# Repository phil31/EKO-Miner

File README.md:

# EKO-Miner

repository of EKO Miner designs

#### Inspired by the [Bitaxe](https://github.com/skot/bitaxe) and [OSMU fundation] (https://osmu.wiki/)

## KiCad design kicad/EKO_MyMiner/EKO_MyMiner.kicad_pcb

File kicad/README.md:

## BOX Miner

#### The EKO-Miner is a stackable and rackable ASIC Bitcoin miner that utilizes hashcards. The hashcards are capable of mining Bitcoin by themselves or multiple. The concept of hashcards is highly scalable and offers a clean and streamlined approach to Bitcoin mining.

Miner Box Supports up to 3 ASIC Hashcards. An ATX PSU is required.

- Rackable miner boards based on specifics ASIC Hashboards, generic power supply and driven by an ESP32
- WIFI and ETHERNET connectivity
- TFT RGB LCD 172x320 display
- External standard ATX power supply
- Watercooling for quiet operation

Power board : 
	- designed with TPS53667 / 5 Phases / 0.5 to 2.5V, up to 300Watts

AsicBoards : 
- 16 x BM1366 : 8 TH/s - Efficiency 25J/TH
- 16 x BM1368 : 9.5 TH/s - Efficiency 18J/TH
- 10 x BM1370 : 10 TH/s - Efficiency 15J/TH
	
enclosure box dimensions: 200 x 200 x 140 mm

## NerdEKO-GammaFork-NoATX Miner
fork of the NerdOCTAXE-Gamma design (https://github.com/Patsch91/NerdOCTAXE-Gamma), with 12 x BM1370 (12TH/s SHA256)

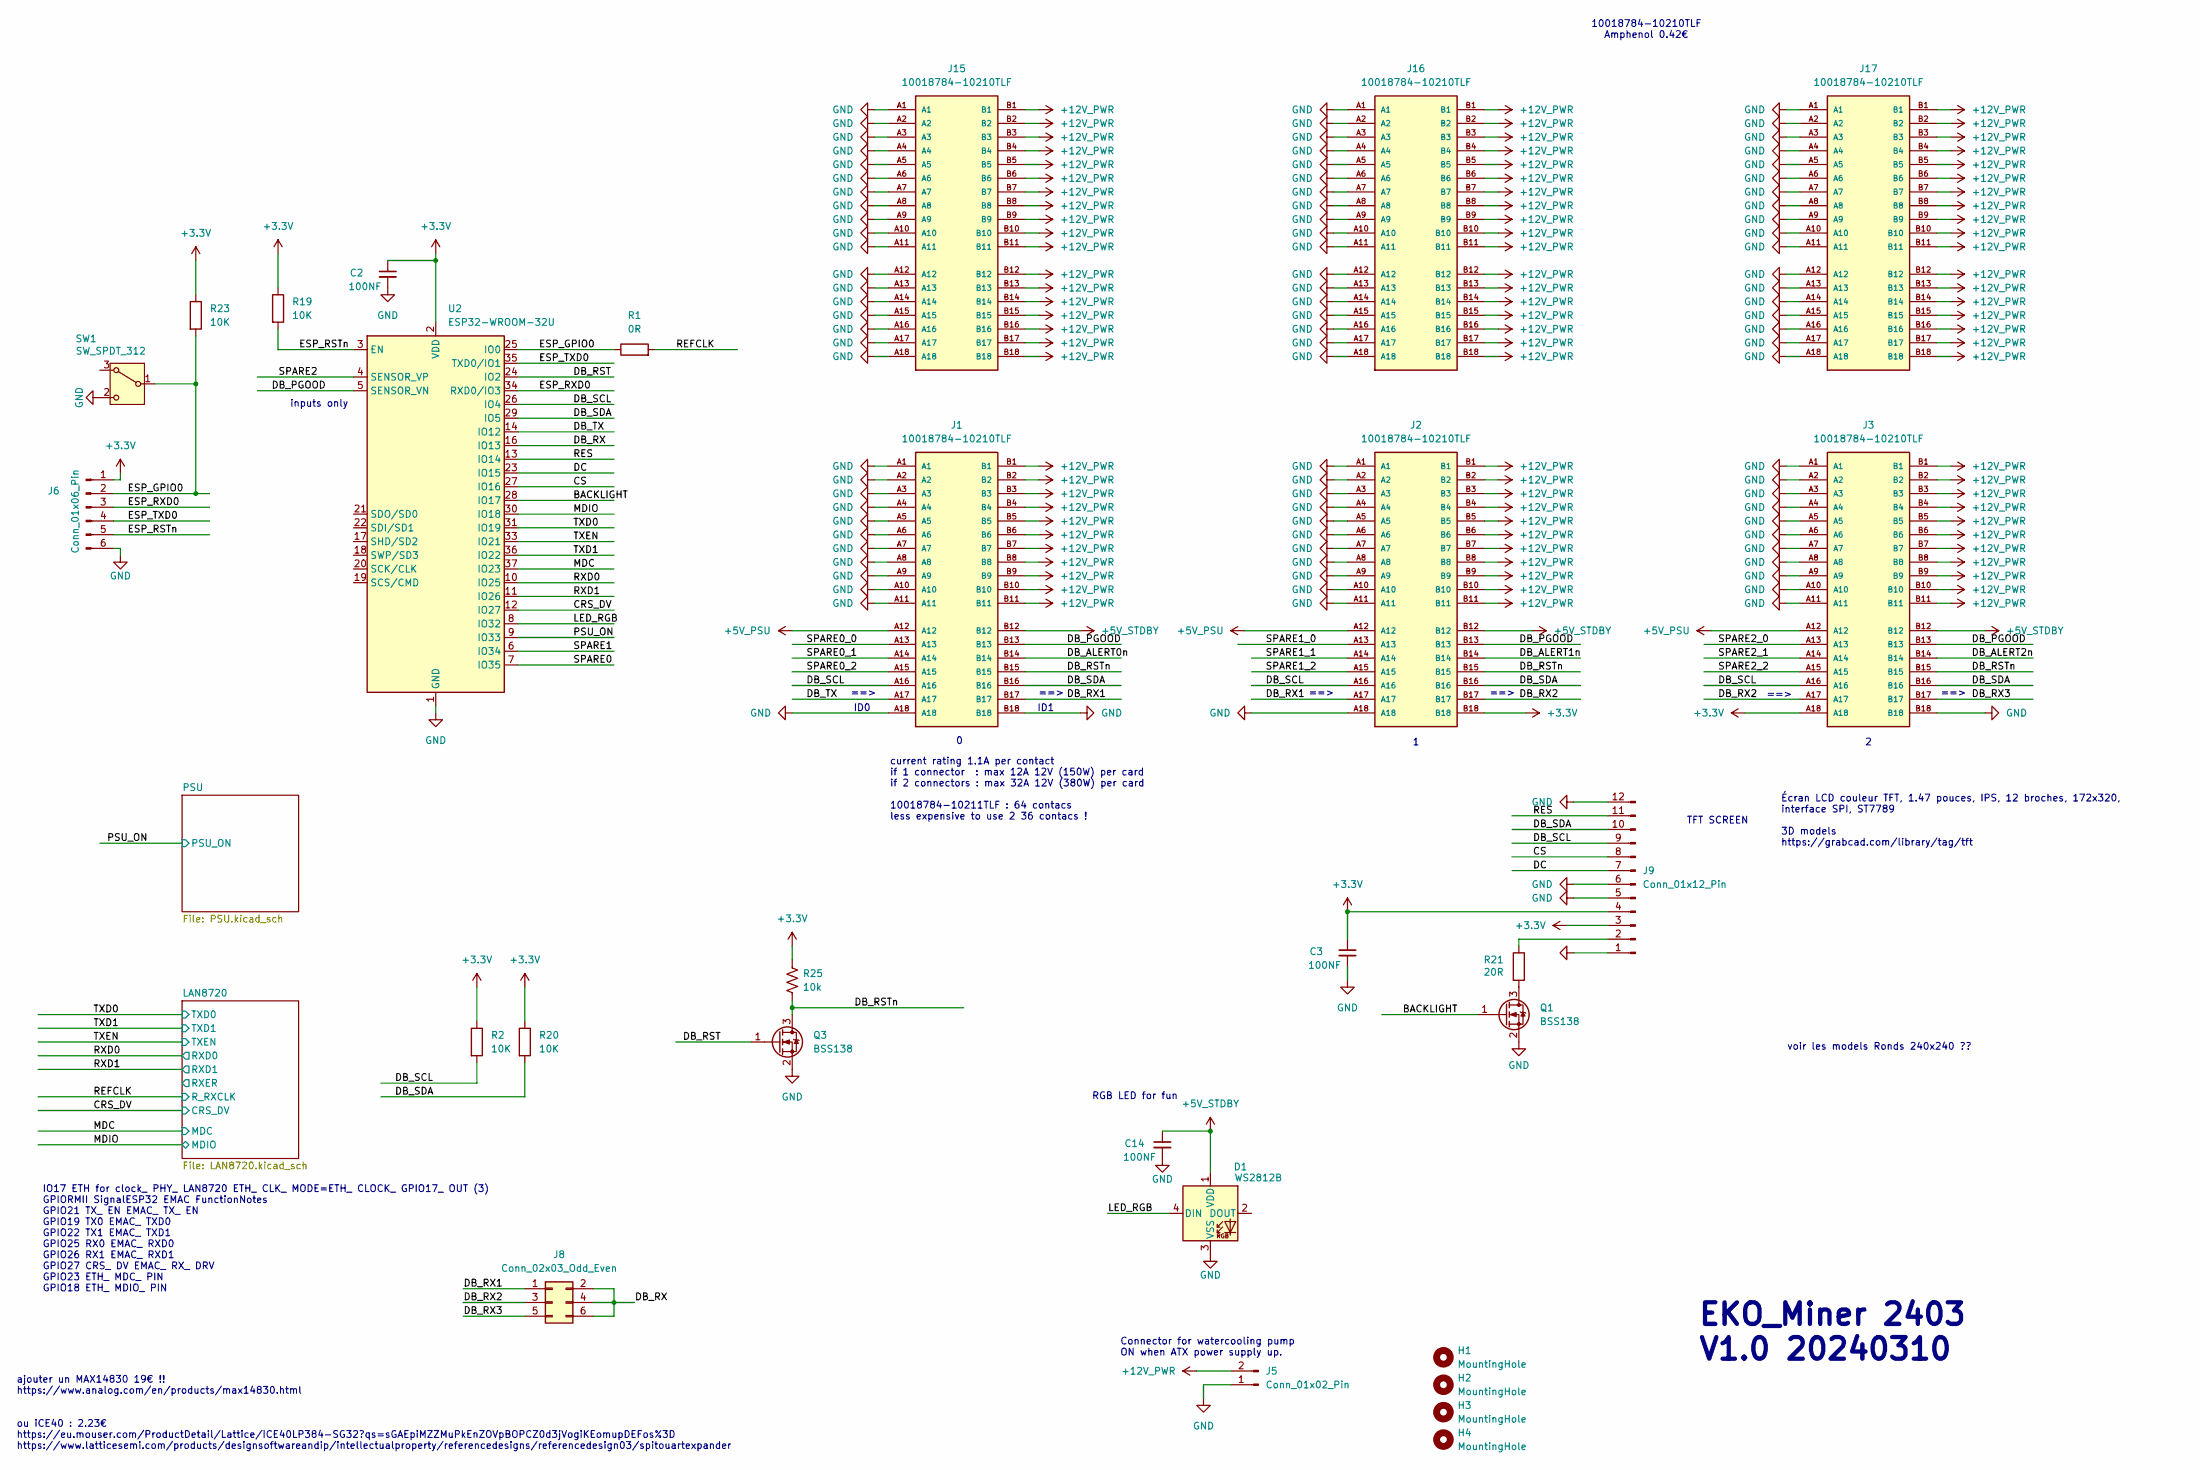
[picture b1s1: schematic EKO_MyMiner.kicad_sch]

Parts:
C2, C3, C14: 100NF; C_0603_1608Metric
D1: WS2812B; LED_WS2812B_PLCC4_5.0x5.0mm_P3.2mm
H1, H2, H3, H4: MountingHole; MountingHole_3.2mm_M3_DIN965_Pad
J1, J2, J3, J15, J16, J17: 10018784-10210TLF; AMPHENOL_10018784-10210TLF; PARTREV S
J5: Conn_01x02_Pin; JST_EH_B2B-EH-A_1x02_P2.50mm_Vertical
J6: Conn_01x06_Pin; EKO_ESP_ISP
J8: Conn_02x03_Odd_Even; PinHeader_2x03_P2.54mm_Vertical
J9: Conn_01x12_Pin; LCD LBS147TC-IG01
Q1, Q3: BSS138; SOT-23
R1: 0R; R_0603_1608Metric
R2, R19, R20, R23: 10K; R_0603_1608Metric
R21: 20R; R_0603_1608Metric
R25: 10k; R_0402_1005Metric; PARTNO RC0402JR-0710KL
SW1: SW_SPDT_312; SW_PUSH_6mm_H9.5mm
U2: ESP32-WROOM-32U

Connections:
+3.3V: C2.1, C3.1, J2.B18, J3.A18, J6.1, J9.3, J9.4, R2.1, R19.1, R20.1, R23.1, R25.2, U2.2 (VDD); also elsewhere on the board
+5V_PSU: J1.A12, J2.A12, J3.A12; also elsewhere on the board
+5V_STDBY: C14.1, D1.1 (VDD), J1.B12, J2.B12, J3.B12; also elsewhere on the board
+12V_PWR: J1.B1, J1.B2, J1.B3, J1.B4, J1.B5, J1.B6, J1.B7, J1.B8, J1.B9, J1.B10, J1.B11, J2.B1, J2.B2, J2.B3, J2.B4, J2.B5, J2.B6, J2.B7, J2.B8, J2.B9, J2.B10, J2.B11, J3.B1, J3.B2, J3.B3, J3.B4, J3.B5, J3.B6, J3.B7, J3.B8, J3.B9, J3.B10, J3.B11, J5.2, J15.B1, J15.B2, J15.B3, J15.B4, J15.B5, J15.B6, J15.B7, J15.B8, J15.B9, J15.B10, J15.B11, J15.B12, J15.B13, J15.B14, J15.B15, J15.B16, J15.B17, J15.B18, J16.B1, J16.B2, J16.B3, J16.B4, J16.B5, J16.B6, J16.B7, J16.B8, J16.B9, J16.B10, J16.B11, J16.B12, J16.B13, J16.B14, J16.B15, J16.B16, J16.B17, J16.B18, J17.B1, J17.B2, J17.B3, J17.B4, J17.B5, J17.B6, J17.B7, J17.B8, J17.B9, J17.B10, J17.B11, J17.B12, J17.B13, J17.B14, J17.B15, J17.B16, J17.B17, J17.B18; also elsewhere on the board
/BACKLIGHT: Q1.1 (G), U2.28 (IO17)
/CRS_DV: U2.12 (IO27); also elsewhere on the board
/CS: J9.8, U2.27 (IO16)
/DB_ALERT0n: J1.B14
/DB_ALERT1n: J2.B14
/DB_ALERT2n: J3.B14
/DB_PGOOD: J1.B13, J2.B13, J3.B13, U2.5 (SENSOR_VN)
/DB_RST: Q3.1 (G), U2.24 (IO2)
/DB_RSTn: J1.B15, J2.B15, J3.B15, Q3.3 (D), R25.1
/DB_RX: J8.2, J8.4, J8.6, U2.16 (IO13)
/DB_RX1: J1.B17, J2.A17, J8.1
/DB_RX2: J2.B17, J3.A17, J8.3
/DB_RX3: J3.B17, J8.5
/DB_SCL: J1.A16, J2.A16, J3.A16, J9.9, R2.2, U2.26 (IO4)
/DB_SDA: J1.B16, J2.B16, J3.B16, J9.10, R20.2, U2.29 (IO5)
/DB_TX: J1.A17, U2.14 (IO12)
/DC: J9.7, U2.23 (IO15)
/ESP_GPIO0: J6.2, R1.1, R23.2, SW1.1 (B), U2.25 (IO0)
/ESP_RSTn: J6.5, R19.2, U2.3 (EN)
/ESP_RXD0: J6.3, U2.34 (RXD0/IO3)
/ESP_TXD0: J6.4, U2.35 (TXD0/IO1)
/LED_RGB: D1.4 (DIN), U2.8 (IO32)
/MDC: U2.37 (IO23); also elsewhere on the board
/MDIO: U2.30 (IO18); also elsewhere on the board
/PSU_ON: U2.9 (IO33); also elsewhere on the board
/REFCLK: R1.2; also elsewhere on the board
/RES: J9.11, U2.13 (IO14)
/RXD0: U2.10 (IO25); also elsewhere on the board
/RXD1: U2.11 (IO26); also elsewhere on the board
/SPARE0: U2.7 (IO35)
/SPARE0_0: J1.A13
/SPARE0_1: J1.A14
/SPARE0_2: J1.A15
/SPARE1: U2.6 (IO34)
/SPARE1_0: J2.A13
/SPARE1_1: J2.A14
/SPARE1_2: J2.A15
/SPARE2: U2.4 (SENSOR_VP)
/SPARE2_0: J3.A13
/SPARE2_1: J3.A14
/SPARE2_2: J3.A15
/TXD0: U2.31 (IO19); also elsewhere on the board
/TXD1: U2.36 (IO22); also elsewhere on the board
/TXEN: U2.33 (IO21); also elsewhere on the board
GND: C2.2, C3.2, C14.2, D1.3 (VSS), J1.A1, J1.A2, J1.A3, J1.A4, J1.A5, J1.A6, J1.A7, J1.A8, J1.A9, J1.A10, J1.A11, J1.A18, J1.B18, J2.A1, J2.A2, J2.A3, J2.A4, J2.A5, J2.A6, J2.A7, J2.A8, J2.A9, J2.A10, J2.A11, J2.A18, J3.A1, J3.A2, J3.A3, J3.A4, J3.A5, J3.A6, J3.A7, J3.A8, J3.A9, J3.A10, J3.A11, J3.B18, J5.1, J6.6, J9.1, J9.5, J9.6, J9.12, J15.A1, J15.A2, J15.A3, J15.A4, J15.A5, J15.A6, J15.A7, J15.A8, J15.A9, J15.A10, J15.A11, J15.A12, J15.A13, J15.A14, J15.A15, J15.A16, J15.A17, J15.A18, J16.A1, J16.A2, J16.A3, J16.A4, J16.A5, J16.A6, J16.A7, J16.A8, J16.A9, J16.A10, J16.A11, J16.A12, J16.A13, J16.A14, J16.A15, J16.A16, J16.A17, J16.A18, J17.A1, J17.A2, J17.A3, J17.A4, J17.A5, J17.A6, J17.A7, J17.A8, J17.A9, J17.A10, J17.A11, J17.A12, J17.A13, J17.A14, J17.A15, J17.A16, J17.A17, J17.A18, Q1.2 (S), Q3.2 (S), SW1.2 (C), U2.1 (GND), U2.15 (GND), U2.38 (GND), U2.39 (GND); also elsewhere on the board
unnamed: J9.2, R21.1
unnamed: Q1.3 (D), R21.2

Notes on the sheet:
current rating 1.1A per contact if 1 connector : max 12A 12V (150W) per card if 2 connectors : max 32A 12V (380W) per card 10018784-10211TLF : 64 contacs less expensive to use 2 36 contacs !
10018784-10210TLF Amphenol 0.42€
voir les models Ronds 240x240 ??
TFT SCREEN
==>
ajouter un MAX14830 19€ !! https://www.analog.com/en/products/max14830.html ou iCE40 : 2.23€ https://eu.mouser.com/ProductDetail/Lattice/ICE40LP384-SG32?qs=sGAEpiMZZMuPkEnZOVpBOPCZ0d3jVogiKEomupDEFos%3D https://www.latticesemi.com/products/designsoftwareandip/intellectualproperty/referencedesigns/r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
Connector for watercooling pump ON when ATX power supply up.
ID0
Écran LCD couleur TFT, 1.47 pouces, IPS, 12 broches, 172x320, interface SPI, ST7789 3D models https://grabcad.com/library/tag/tft
inputs only
IO17 ETH for clock_ PHY_ LAN8720 ETH_ CLK_ MODE=ETH_ CLOCK_ GPIO17_ OUT (3) GPIORMII SignalESP32 EMAC FunctionNotes GPIO21 TX_ EN EMAC_ TX_ EN GPIO19 TX0 EMAC_ TXD0 GPIO22 TX1 EMAC_ TXD1 GPIO25 RX0 EMAC_ RXD0 GPIO26 RX1 EMAC_ RXD1 GPIO27 CRS_ DV EMAC_ RX_ DRV GPIO23 ETH_ MDC_ PIN GPIO18 ETH_ MDIO_ 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
RGB LED for fun
ID1
EKO_Miner 2403 V1.0 20240310

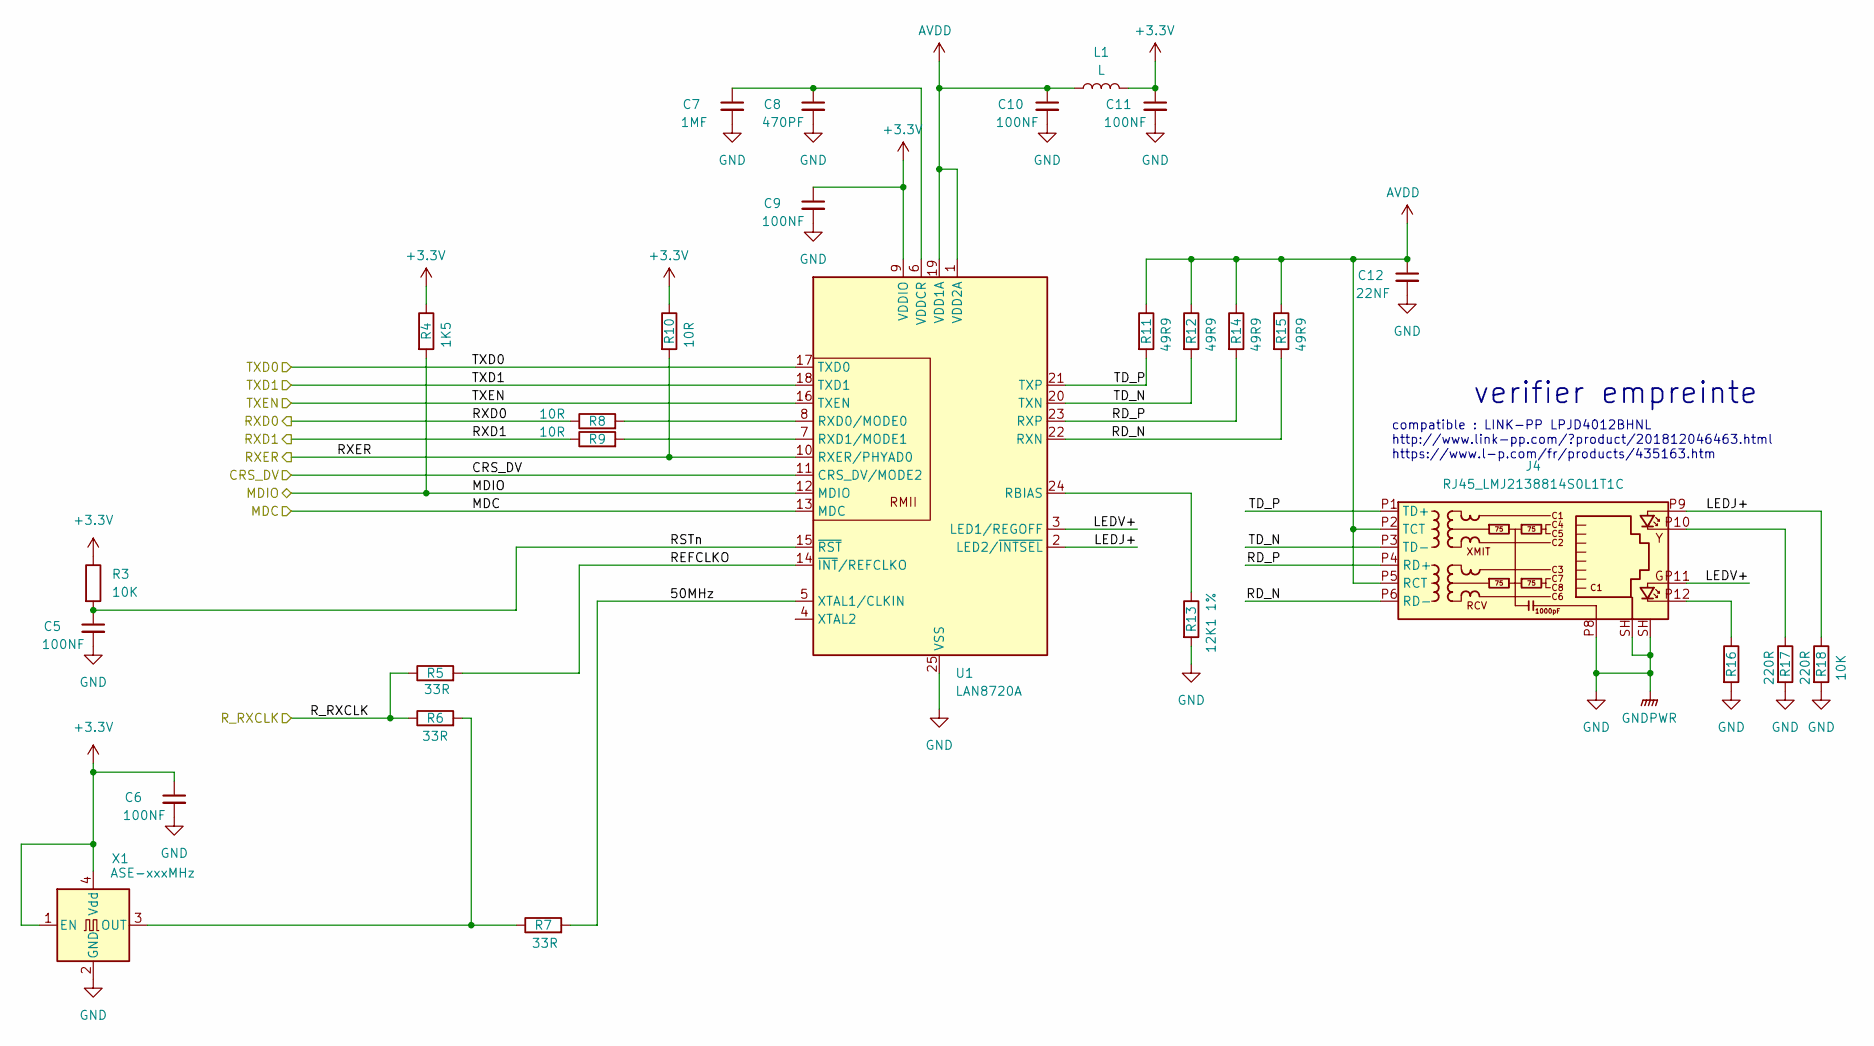
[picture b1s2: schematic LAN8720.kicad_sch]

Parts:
C5, C6, C9, C10, C11: 100NF; C_0603_1608Metric
C7: 1MF; C_0603_1608Metric
C8: 470PF; C_0603_1608Metric
C12: 22NF; C_0603_1608Metric
J4: RJ45_LMJ2138814S0L1T1C; LMJ2138814SOL1T1C
L1: L; L_0805_2012Metric
R3, R18: 10K; R_0603_1608Metric
R4: 1K5; R_0603_1608Metric
R5, R6, R7: 33R; R_0603_1608Metric
R8, R9, R10: 10R; R_0603_1608Metric
R11, R12, R14, R15: 49R9; R_0603_1608Metric
R13: 12K1 1%; R_0603_1608Metric
R16, R17: 220R; R_0603_1608Metric
U1: LAN8720A; VQFN-24-1EP_4x4mm_P0.5mm_EP2.5x2.5mm_ThermalVias
X1: ASE-xxxMHz; Oscillator_SMD_Abracon_ASE-4Pin_3.2x2.5mm

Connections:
+3.3V: C6.1, C9.1, C11.1, L1.2, R3.1, R4.1, R10.1, U1.9 (VDDIO), X1.1 (EN), X1.4 (Vdd); also elsewhere on the board
/CRS_DV: U1.11 (CRS_DV/MODE2); also elsewhere on the board
/LAN8720/50MHz: R7.2, U1.5 (XTAL1/CLKIN)
/LAN8720/LEDJ+: J4.P9, R18.1, U1.2 (LED2/~INTSEL)
/LAN8720/LEDV+: J4.P11, U1.3 (LED1/REGOFF)
/LAN8720/RD_N: J4.P6 (RD-), R15.2, U1.22 (RXN)
/LAN8720/RD_P: J4.P4 (RD+), R14.2, U1.23 (RXP)
/LAN8720/REFCLKO: R5.2, U1.14 (~INT/REFCLKO)
/LAN8720/RSTn: C5.1, R3.2, U1.15 (~RST)
/LAN8720/RXER: R10.2, U1.10 (RXER/PHYAD0)
/LAN8720/TD_N: J4.P3 (TD-), R12.2, U1.20 (TXN)
/LAN8720/TD_P: J4.P1 (TD+), R11.2, U1.21 (TXP)
/MDC: U1.13 (MDC); also elsewhere on the board
/MDIO: R4.2, U1.12 (MDIO); also elsewhere on the board
/REFCLK: R5.1, R6.1; also elsewhere on the board
/RXD0: R8.1; also elsewhere on the board
/RXD1: R9.1; also elsewhere on the board
/TXD0: U1.17 (TXD0); also elsewhere on the board
/TXD1: U1.18 (TXD1); also elsewhere on the board
/TXEN: U1.16 (TXEN); also elsewhere on the board
AVDD: C10.1, C12.1, J4.P2 (TCT), J4.P5 (RCT), L1.1, R11.1, R12.1, R14.1, R15.1, U1.1 (VDD2A), U1.19 (VDD1A)
GND: C5.2, C6.2, C7.2, C8.2, C9.2, C10.2, C11.2, C12.2, J4.P8, J4.SH, R13.2, R16.2, R17.2, R18.2, U1.25 (VSS), X1.2 (GND); also elsewhere on the board
unnamed: J4.P10, R17.1
unnamed: J4.P12, R16.1
unnamed: R13.1, U1.24 (RBIAS)
unnamed: R8.2, U1.8 (RXD0/MODE0)
unnamed: R9.2, U1.7 (RXD1/MODE1)
unnamed: C7.1, C8.1, U1.6 (VDDCR)
unnamed: R6.2, R7.1, X1.3 (OUT)

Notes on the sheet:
compatible : LINK-PP LPJD4012BHNL http://www.link-pp.com/?product/201812046463.html https://www.l-p.com/fr/products/435163.htm
verifier empreinte

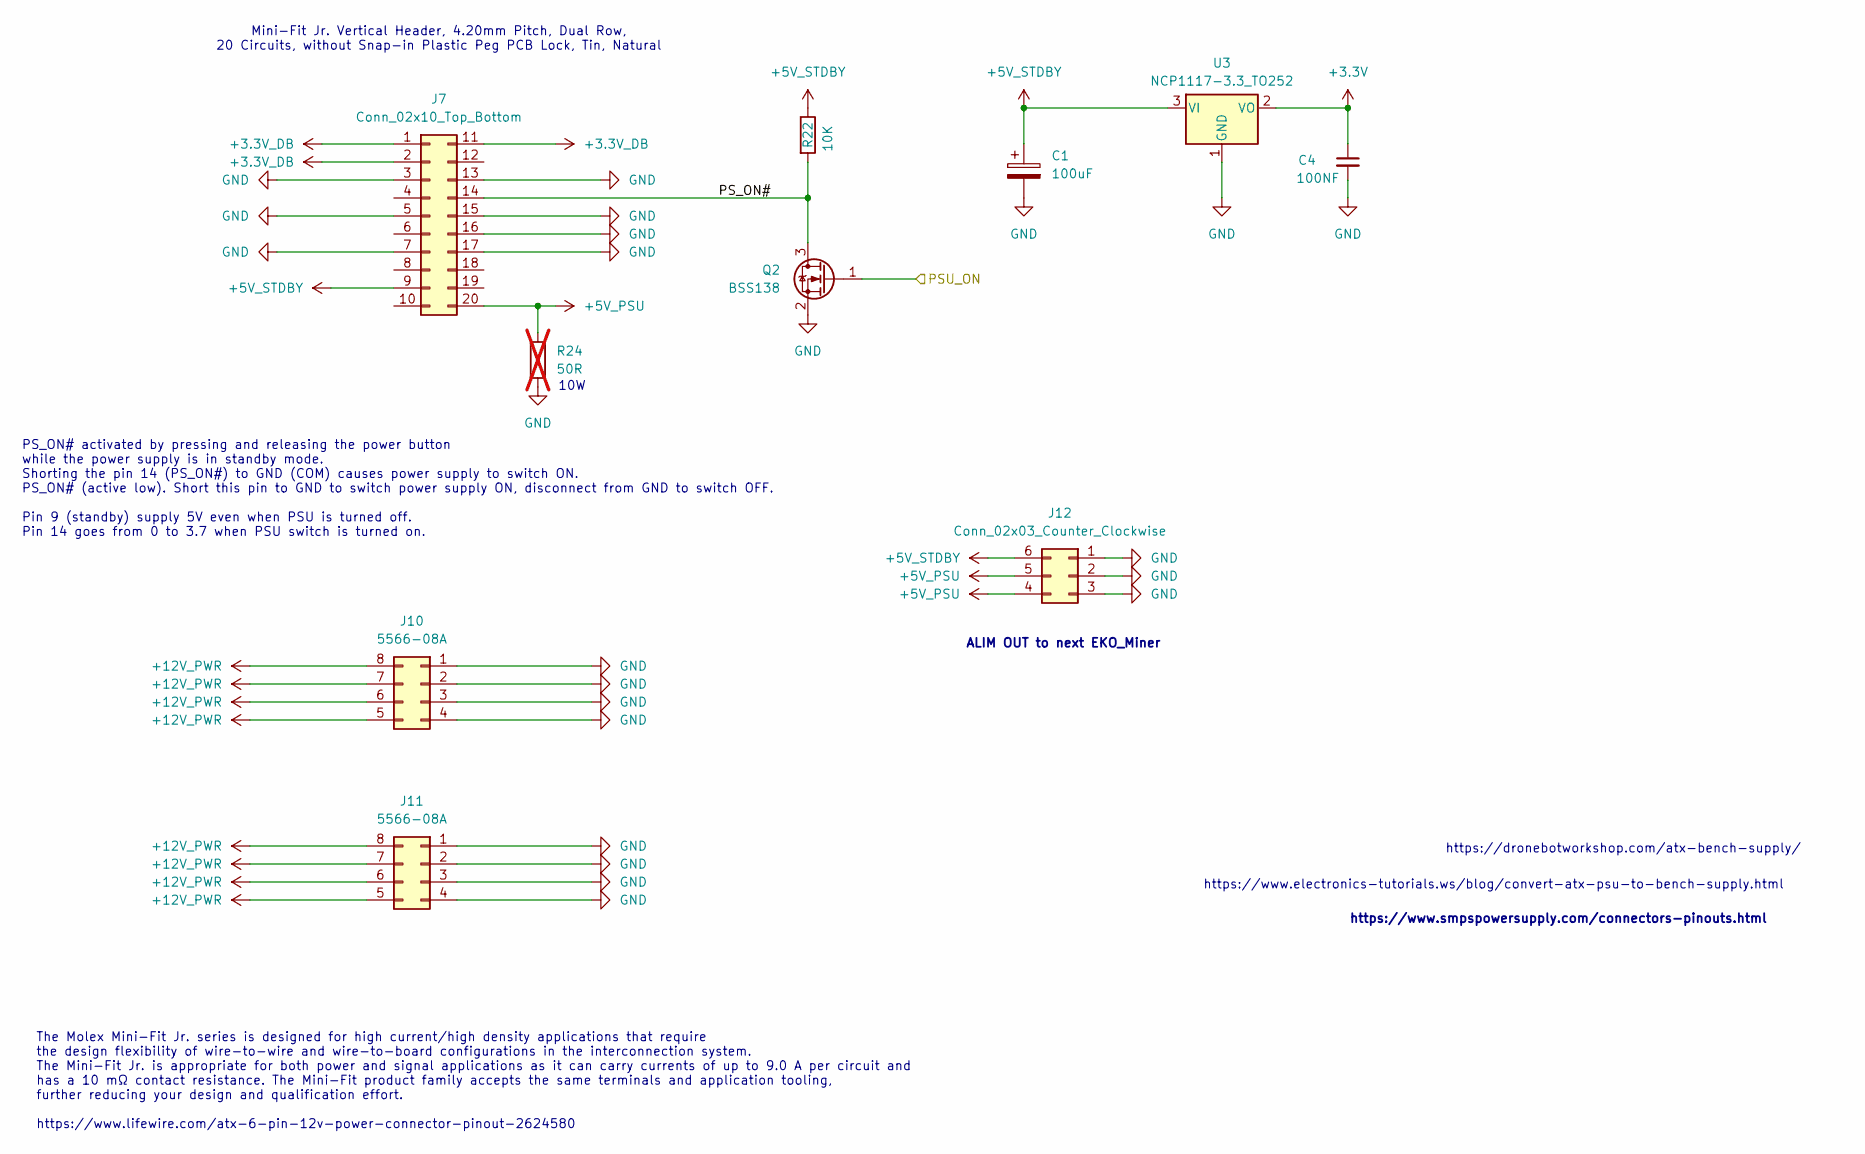
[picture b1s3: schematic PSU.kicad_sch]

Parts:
C1: 100uF; CP_Elec_5x5.7
C4: 100NF; C_0603_1608Metric
J7: Conn_02x10_Top_Bottom; Molex_Mini-Fit_Jr_5566-20A_2x10_P4.20mm_Vertical
J10, J11: 5566-08A; Molex_Mini-Fit_Jr_5566-08A2_2x04_P4.20mm_Vertical
J12: Conn_02x03_Counter_Clockwise; Molex_Mini-Fit_Jr_5566-06A2_2x03_P4.20mm_Vertical
Q2: BSS138; SOT-23
R22: 10K; R_0603_1608Metric
R24: 50R; R_Axial_Power_L25.0mm_W6.4mm_P27.94mm; not fitted
U3: NCP1117-3.3_TO252; TO-252-2

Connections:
+3.3V: C4.1, U3.2 (VO); also elsewhere on the board
+3.3V_DB: J7.1, J7.2, J7.11
+5V_PSU: J7.20, J12.4, J12.5, R24.1; also elsewhere on the board
+5V_STDBY: C1.1, J7.9, J12.6, R22.1, U3.3 (VI); also elsewhere on the board
+12V_PWR: J10.5, J10.6, J10.7, J10.8, J11.5, J11.6, J11.7, J11.8; also elsewhere on the board
/PSU/PS_ON#: J7.14, Q2.3 (D), R22.2
/PSU_ON: Q2.1 (G); also elsewhere on the board
GND: C1.2, C4.2, J7.3, J7.5, J7.7, J7.13, J7.15, J7.16, J7.17, J10.1, J10.2, J10.3, J10.4, J11.1, J11.2, J11.3, J11.4, J12.1, J12.2, J12.3, Q2.2 (S), R24.2, U3.1 (GND); also elsewhere on the board

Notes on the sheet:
The Molex Mini-Fit Jr. series is designed for high current/high density applications that require the design flexibility of wire-to-wire and wire-to-board configurations in the interconnection system. The Mini-Fit Jr. is appropriate for both power and signal applications as it can carry currents of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
https://www.smpspowersupply.com/connectors-pinouts.html
https://dronebotworkshop.com/atx-bench-supply/
Mini-Fit Jr. Vertical Header, 4.20mm Pitch, Dual Row, 20 Circuits, without Snap-in Plastic Peg PCB Lock, Tin, Natural
PS_ON# activated by pressing and releasing the power button while the power supply is in standby mode. Shorting the pin 14 (PS_ON#) to GND (COM) causes power supply to switch ON. PS_ON# (active low). Short this pin to GND to switch power supply ON, disconnect from GND to switch OFF. Pin 9 (standby)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
https://www.electronics-tutorials.ws/blog/convert-atx-psu-to-bench-supply.html
10W
ALIM OUT to next EKO_Miner

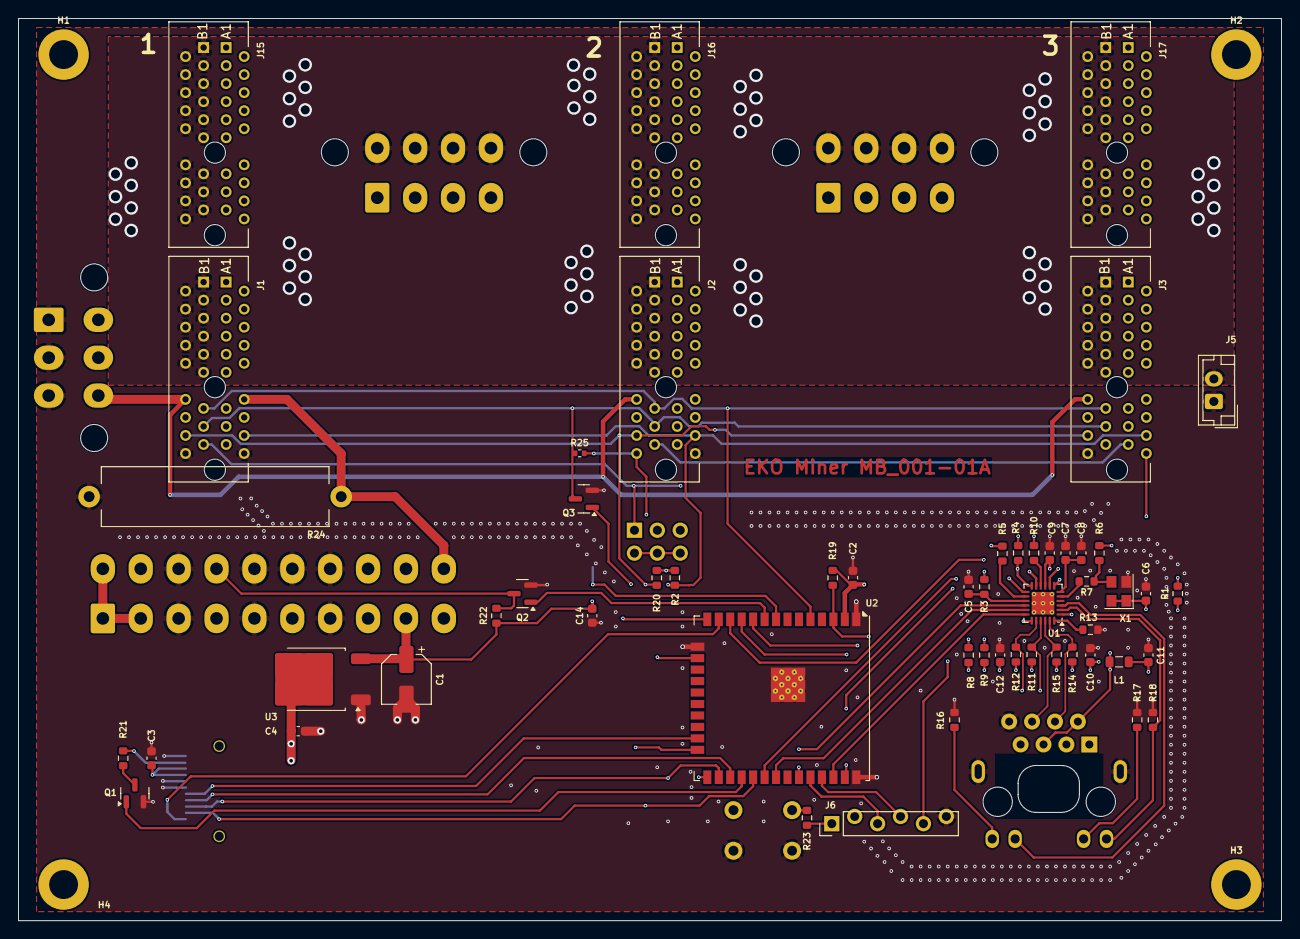
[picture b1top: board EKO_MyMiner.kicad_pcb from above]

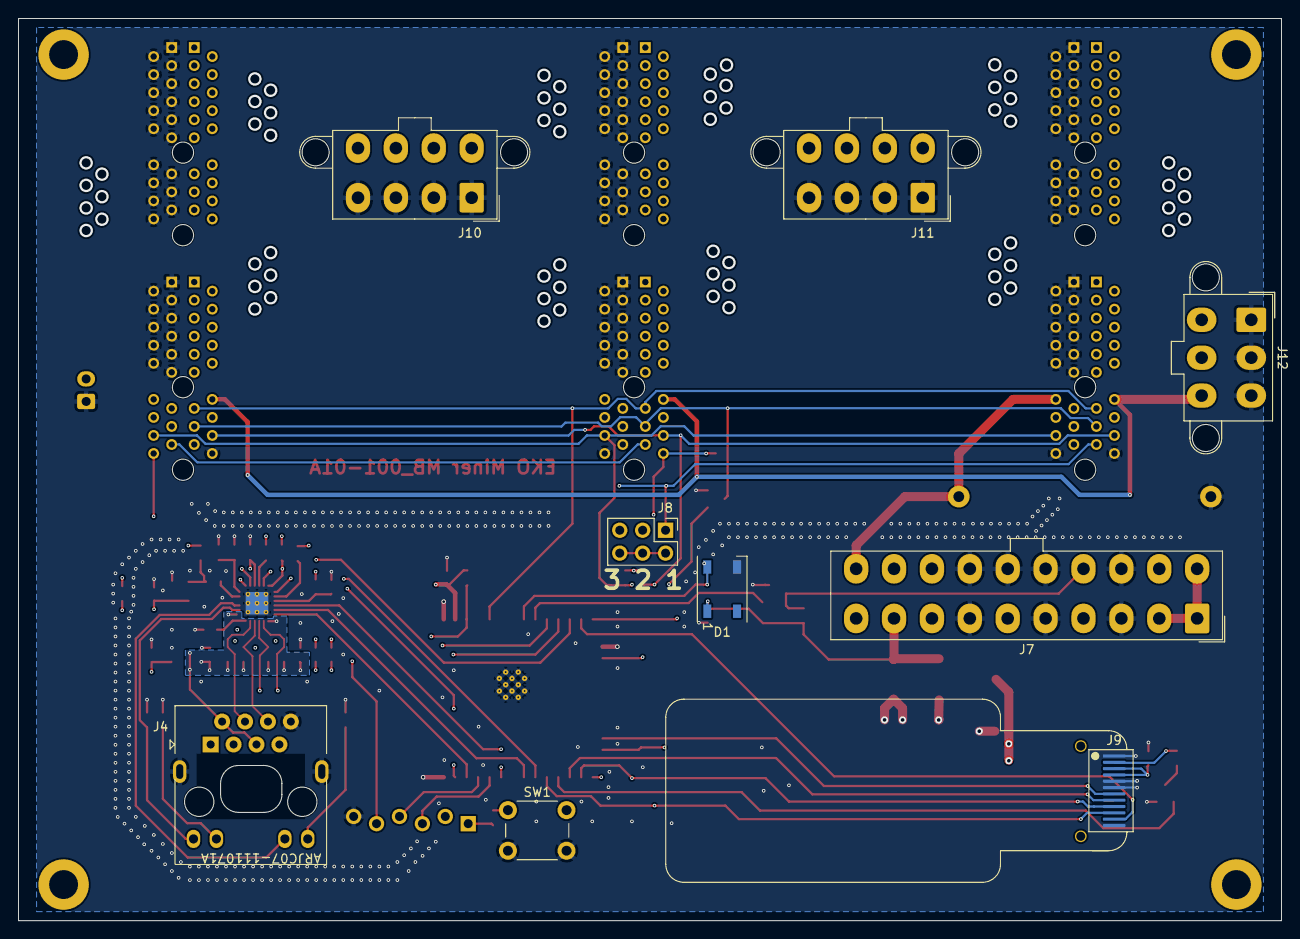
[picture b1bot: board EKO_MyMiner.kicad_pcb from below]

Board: 4 copper layers, 140.0 x 100.0 mm, 67 parts (9 on the bottom side), 56 nets.

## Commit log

2024-04-02 init repo
    first commit Motherboard and Daughterboard with 8 BM1366
2024-05-14 first release
    Kicad 8.0 schematics and PCB of the Mother and the Daughter board.
    First Daughter board is 16 x BM1366 ASICs
    *** BE AWARE *** all 3D documents are not fully validate
2024-05-31 hashcard images
2024-06-01 cleanup
2024-06-20 add images
2024-06-23 update pics
2024-06-27 cleaning older files
2024-07-21 upload option 1 ( original ESPminer fw with a new device model)
    some issues during the link operation .. can't solve the error :(
2024-12-07 reorder directory
2024-12-07 update 3D directory
    update 3D directory
2024-12-07 update 3D models
